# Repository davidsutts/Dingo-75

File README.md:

# Dingo-75

The Dingo 75 is intended to be a budget 75% keyboard PCB that anyone can print and assemble. The PCB runs on an Atmel AT90USB1286.

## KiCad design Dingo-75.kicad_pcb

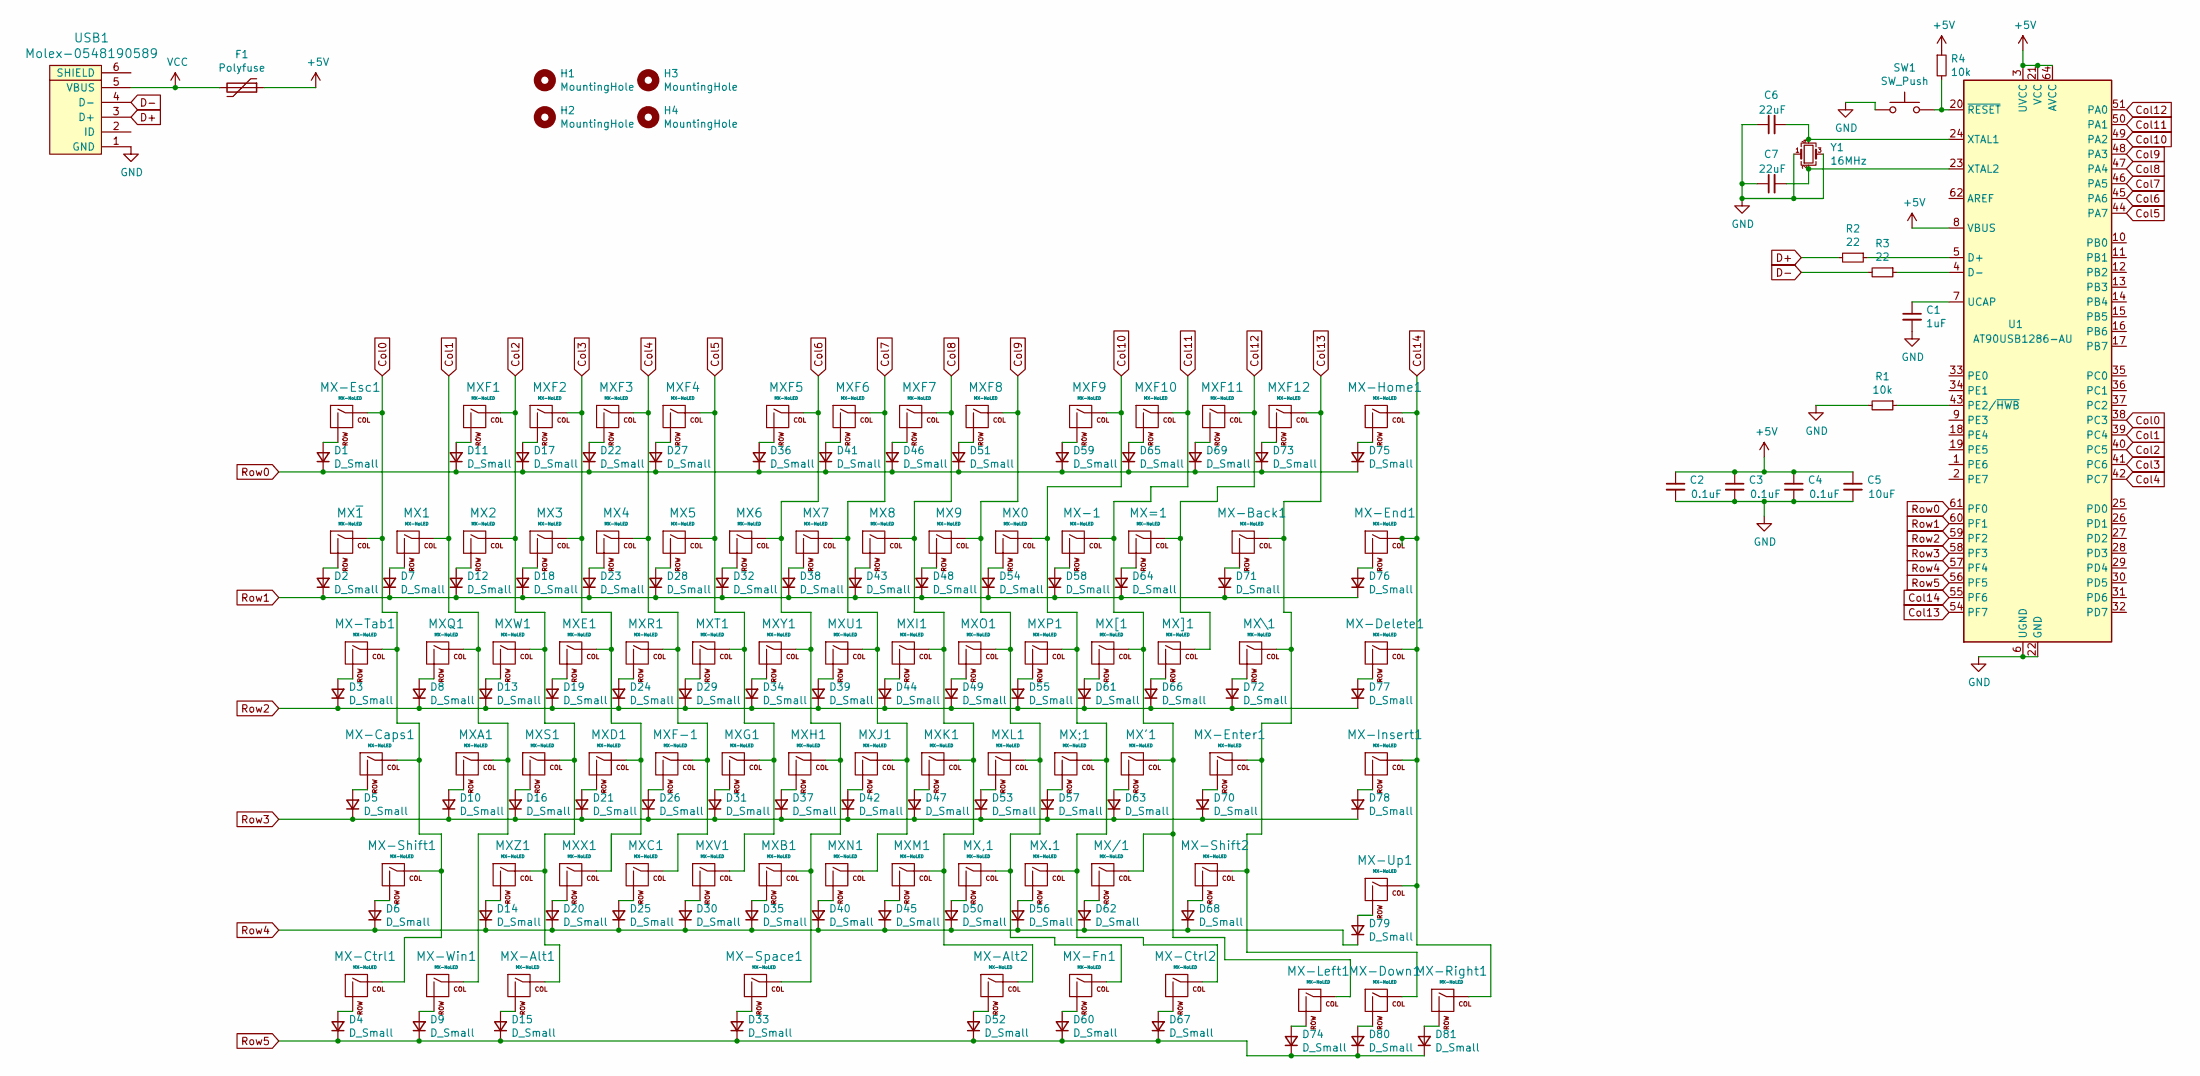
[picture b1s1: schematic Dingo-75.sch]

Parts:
C1: 1uF; C_0805_2012Metric
C2, C3, C4: 0.1uF; C_0805_2012Metric
C5: 10uF; C_0805_2012Metric
C6, C7: 22uF; C_0805_2012Metric
D1, D2, D3, D4, D5, D6, D7, D8, D9, D10, D11, D12, D13, D14, D15, D16, D17, D18, D19, D20, D21, D22, D23, D24, D25, D26, D27, D28, D29, D30, D31, D32, D33, D34, D35, D36, D37, D38, D39, D40, D41, D42, D43, D44, D45, D46, D47, D48, D49, D50, D51, D52, D53, D54, D55, D56, D57, D58, D59, D60, D61, D62, D63, D64, D65, D66, D67, D68, D69, D70, D71, D72, D73, D74, D75, D76, D77, D78, D79, D80, D81: D_Small; D_SOD-123
F1: Polyfuse; Fuse_1206_3216Metric
H1, H2, H3, H4: MountingHole; MountingHole_2mm
MX0, MX1, MX2, MX3, MX4, MX5, MX6, MX7, MX8, MX9, MX.1: MX-NoLED; MX-1U-NoLED
MX'1: MX-NoLED; MX-1U-NoLED
MX,1: MX-NoLED; MX-1U-NoLED
MX-1: MX-NoLED; MX-1U-NoLED
MX-Alt1, MX-Alt2: MX-NoLED; MX-1U-NoLED
MX-Back1: MX-NoLED; MX-1U-NoLED
MX-Caps1: MX-NoLED; MX-1U-NoLED
MX-Ctrl1, MX-Ctrl2: MX-NoLED; MX-1U-NoLED
MX-Delete1: MX-NoLED; MX-1U-NoLED
MX-Down1: MX-NoLED; MX-1U-NoLED
MX-End1: MX-NoLED; MX-1U-NoLED
MX-Enter1: MX-NoLED; MX-1U-NoLED
MX-Esc1: MX-NoLED; MX-1U-NoLED
MX-Fn1: MX-NoLED; MX-1U-NoLED
MX-Home1: MX-NoLED; MX-1U-NoLED
MX-Insert1: MX-NoLED; MX-1U-NoLED
MX-Left1: MX-NoLED; MX-1U-NoLED
MX-Right1: MX-NoLED; MX-1U-NoLED
MX-Shift1, MX-Shift2: MX-NoLED; MX-1U-NoLED
MX-Space1: MX-NoLED; MX-1U-NoLED
MX-Tab1: MX-NoLED; MX-1U-NoLED
MX-Up1: MX-NoLED; MX-1U-NoLED
MX-Win1: MX-NoLED; MX-1U-NoLED
MX/1: MX-NoLED; MX-1U-NoLED
MX;1: MX-NoLED; MX-1U-NoLED
MX=1: MX-NoLED; MX-1U-NoLED
MXA1: MX-NoLED; MX-1U-NoLED
MXB1: MX-NoLED; MX-1U-NoLED
MXC1: MX-NoLED; MX-1U-NoLED
MXD1: MX-NoLED; MX-1U-NoLED
MXE1: MX-NoLED; MX-1U-NoLED
MXF1, MXF2, MXF3, MXF4, MXF5, MXF6, MXF7, MXF8, MXF9, MXF10, MXF11, MXF12: MX-NoLED; MX-1U-NoLED
MXF-1: MX-NoLED; MX-1U-NoLED
MXG1: MX-NoLED; MX-1U-NoLED
MXH1: MX-NoLED; MX-1U-NoLED
MXI1: MX-NoLED; MX-1U-NoLED
MXJ1: MX-NoLED; MX-1U-NoLED
MXK1: MX-NoLED; MX-1U-NoLED
MXL1: MX-NoLED; MX-1U-NoLED
MXM1: MX-NoLED; MX-1U-NoLED
MXN1: MX-NoLED; MX-1U-NoLED
MXO1: MX-NoLED; MX-1U-NoLED
MXP1: MX-NoLED; MX-1U-NoLED
MXQ1: MX-NoLED; MX-1U-NoLED
MXR1: MX-NoLED; MX-1U-NoLED
MXS1: MX-NoLED; MX-1U-NoLED
MXT1: MX-NoLED; MX-1U-NoLED
MXU1: MX-NoLED; MX-1U-NoLED
MXV1: MX-NoLED; MX-1U-NoLED
MXW1: MX-NoLED; MX-1U-NoLED
MXX1: MX-NoLED; MX-1U-NoLED
MXY1: MX-NoLED; MX-1U-NoLED
MXZ1: MX-NoLED; MX-1U-NoLED
MX[1: MX-NoLED; MX-1U-NoLED
MX\1: MX-NoLED; MX-1U-NoLED
MX]1: MX-NoLED; MX-1U-NoLED
MX~1: MX-NoLED; MX-1U-NoLED
R1, R4: 10k; R_0805_2012Metric
R2, R3: 22; R_0805_2012Metric
SW1: SW_Push; SKQG-1155865
U1: AT90USB1286-AU; TQFP-64_14x14mm_P0.8mm
USB1: Molex-0548190589
Y1: 16MHz; Crystal_SMD_3225-4Pin_3.2x2.5mm

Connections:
+5V: C2.1, C3.1, C4.1, C5.1, F1.1, R4.1, U1.3 (UVCC), U1.8 (VBUS), U1.21 (VCC), U1.52 (VCC), U1.64 (AVCC)
Col0: MX-Caps1.1 (COL), MX-Ctrl1.1 (COL), MX-Esc1.1 (COL), MX-Shift1.1 (COL), MX-Tab1.1 (COL), MX~1.1 (COL), U1.38 (PC3)
Col1: MX1.1 (COL), MX-Win1.1 (COL), MXA1.1 (COL), MXQ1.1 (COL), U1.39 (PC4)
Col2: MX2.1 (COL), MX-Alt1.1 (COL), MXF1.1 (COL), MXS1.1 (COL), MXW1.1 (COL), MXZ1.1 (COL), U1.40 (PC5)
Col3: MX3.1 (COL), MXD1.1 (COL), MXE1.1 (COL), MXF2.1 (COL), MXX1.1 (COL), U1.41 (PC6)
Col4: MX4.1 (COL), MXC1.1 (COL), MXF3.1 (COL), MXF-1.1 (COL), MXR1.1 (COL), U1.42 (PC7)
Col5: MX5.1 (COL), MXF4.1 (COL), MXG1.1 (COL), MXT1.1 (COL), MXV1.1 (COL), U1.44 (PA7)
Col6: MX6.1 (COL), MX-Space1.1 (COL), MXB1.1 (COL), MXF5.1 (COL), MXH1.1 (COL), MXY1.1 (COL), U1.45 (PA6)
Col7: MX7.1 (COL), MXF6.1 (COL), MXJ1.1 (COL), MXN1.1 (COL), MXU1.1 (COL), U1.46 (PA5)
Col8: MX8.1 (COL), MX-Alt2.1 (COL), MXF7.1 (COL), MXI1.1 (COL), MXK1.1 (COL), MXM1.1 (COL), U1.47 (PA4)
Col9: MX9.1 (COL), MX,1.1 (COL), MX-Fn1.1 (COL), MXF8.1 (COL), MXL1.1 (COL), MXO1.1 (COL), U1.48 (PA3)
Col10: MX0.1 (COL), MX-Ctrl2.1 (COL), MX.1.1 (COL), MX;1.1 (COL), MXF9.1 (COL), MXP1.1 (COL), U1.49 (PA2)
Col11: MX'1.1 (COL), MX-1.1 (COL), MX-Left1.1 (COL), MX/1.1 (COL), MXF10.1 (COL), MX[1.1 (COL), U1.50 (PA1)
Col12: MX=1.1 (COL), MXF11.1 (COL), MX]1.1 (COL), U1.51 (PA0)
Col13: MX-Back1.1 (COL), MX-Down1.1 (COL), MX-Enter1.1 (COL), MX-Shift2.1 (COL), MXF12.1 (COL), MX\1.1 (COL), U1.54 (PF7)
Col14: MX-Delete1.1 (COL), MX-End1.1 (COL), MX-Home1.1 (COL), MX-Insert1.1 (COL), MX-Right1.1 (COL), MX-Up1.1 (COL), U1.55 (PF6)
D+: R2.2, USB1.3 (D+)
D-: R3.2, USB1.4 (D-)
GND: C1.2, C2.2, C3.2, C4.2, C5.2, C6.1, C7.1, R1.2, SW1.1, U1.6 (UGND), U1.22 (GND), U1.53 (GND), U1.63 (GND), USB1.1 (GND), Y1.1, Y1.3
unnamed: C1.1, U1.7 (UCAP)
unnamed: C6.2, U1.24 (XTAL1), Y1.4
unnamed: C7.2, U1.23 (XTAL2), Y1.2
unnamed: D1.2 (A), MX-Esc1.2 (ROW)
unnamed: D2.2 (A), MX~1.2 (ROW)
unnamed: D3.2 (A), MX-Tab1.2 (ROW)
unnamed: D4.2 (A), MX-Ctrl1.2 (ROW)
unnamed: D5.2 (A), MX-Caps1.2 (ROW)
unnamed: D6.2 (A), MX-Shift1.2 (ROW)
unnamed: D7.2 (A), MX1.2 (ROW)
unnamed: D8.2 (A), MXQ1.2 (ROW)
unnamed: D9.2 (A), MX-Win1.2 (ROW)
unnamed: D10.2 (A), MXA1.2 (ROW)
unnamed: D11.2 (A), MXF1.2 (ROW)
unnamed: D12.2 (A), MX2.2 (ROW)
unnamed: D13.2 (A), MXW1.2 (ROW)
unnamed: D14.2 (A), MXZ1.2 (ROW)
unnamed: D15.2 (A), MX-Alt1.2 (ROW)
unnamed: D16.2 (A), MXS1.2 (ROW)
unnamed: D17.2 (A), MXF2.2 (ROW)
unnamed: D18.2 (A), MX3.2 (ROW)
unnamed: D19.2 (A), MXE1.2 (ROW)
unnamed: D20.2 (A), MXX1.2 (ROW)
unnamed: D21.2 (A), MXD1.2 (ROW)
unnamed: D22.2 (A), MXF3.2 (ROW)
unnamed: D23.2 (A), MX4.2 (ROW)
unnamed: D24.2 (A), MXR1.2 (ROW)
unnamed: D25.2 (A), MXC1.2 (ROW)
unnamed: D26.2 (A), MXF-1.2 (ROW)
unnamed: D27.2 (A), MXF4.2 (ROW)
unnamed: D28.2 (A), MX5.2 (ROW)
unnamed: D29.2 (A), MXT1.2 (ROW)
unnamed: D30.2 (A), MXV1.2 (ROW)
unnamed: D31.2 (A), MXG1.2 (ROW)
unnamed: D32.2 (A), MX6.2 (ROW)
unnamed: D33.2 (A), MX-Space1.2 (ROW)
unnamed: D34.2 (A), MXY1.2 (ROW)
unnamed: D35.2 (A), MXB1.2 (ROW)
unnamed: D36.2 (A), MXF5.2 (ROW)
unnamed: D37.2 (A), MXH1.2 (ROW)
unnamed: D38.2 (A), MX7.2 (ROW)
unnamed: D39.2 (A), MXU1.2 (ROW)
unnamed: D40.2 (A), MXN1.2 (ROW)
unnamed: D41.2 (A), MXF6.2 (ROW)
unnamed: D42.2 (A), MXJ1.2 (ROW)
unnamed: D43.2 (A), MX8.2 (ROW)
unnamed: D44.2 (A), MXI1.2 (ROW)
unnamed: D45.2 (A), MXM1.2 (ROW)
unnamed: D46.2 (A), MXF7.2 (ROW)
unnamed: D47.2 (A), MXK1.2 (ROW)
unnamed: D48.2 (A), MX9.2 (ROW)
unnamed: D49.2 (A), MXO1.2 (ROW)
unnamed: D50.2 (A), MX,1.2 (ROW)
unnamed: D51.2 (A), MXF8.2 (ROW)
unnamed: D52.2 (A), MX-Alt2.2 (ROW)
unnamed: D53.2 (A), MXL1.2 (ROW)
unnamed: D54.2 (A), MX0.2 (ROW)
unnamed: D55.2 (A), MXP1.2 (ROW)
unnamed: D56.2 (A), MX.1.2 (ROW)
unnamed: D57.2 (A), MX;1.2 (ROW)
unnamed: D58.2 (A), MX-1.2 (ROW)
unnamed: D59.2 (A), MXF9.2 (ROW)
unnamed: D60.2 (A), MX-Fn1.2 (ROW)
unnamed: D61.2 (A), MX[1.2 (ROW)
unnamed: D62.2 (A), MX/1.2 (ROW)
unnamed: D63.2 (A), MX'1.2 (ROW)
unnamed: D64.2 (A), MX=1.2 (ROW)
unnamed: D65.2 (A), MXF10.2 (ROW)
unnamed: D66.2 (A), MX]1.2 (ROW)
unnamed: D67.2 (A), MX-Ctrl2.2 (ROW)
unnamed: D68.2 (A), MX-Shift2.2 (ROW)
unnamed: D69.2 (A), MXF11.2 (ROW)
unnamed: D70.2 (A), MX-Enter1.2 (ROW)
unnamed: D71.2 (A), MX-Back1.2 (ROW)
unnamed: D72.2 (A), MX\1.2 (ROW)
unnamed: D73.2 (A), MXF12.2 (ROW)
unnamed: D74.2 (A), MX-Left1.2 (ROW)
unnamed: D75.2 (A), MX-Home1.2 (ROW)
unnamed: D76.2 (A), MX-End1.2 (ROW)
unnamed: D77.2 (A), MX-Delete1.2 (ROW)
unnamed: D78.2 (A), MX-Insert1.2 (ROW)
unnamed: D79.2 (A), MX-Up1.2 (ROW)
unnamed: D80.2 (A), MX-Down1.2 (ROW)
unnamed: D81.2 (A), MX-Right1.2 (ROW)
unnamed: R1.1, U1.43 (PE2/~HWB)
unnamed: R2.1, U1.5 (D+)
unnamed: R3.1, U1.4 (D-)
unnamed: R4.2, SW1.2, U1.20 (~RESET)
Row0: D1.1 (K), D11.1 (K), D17.1 (K), D22.1 (K), D27.1 (K), D36.1 (K), D41.1 (K), D46.1 (K), D51.1 (K), D59.1 (K), D65.1 (K), D69.1 (K), D73.1 (K), D75.1 (K), U1.61 (PF0)
Row1: D2.1 (K), D7.1 (K), D12.1 (K), D18.1 (K), D23.1 (K), D28.1 (K), D32.1 (K), D38.1 (K), D43.1 (K), D48.1 (K), D54.1 (K), D58.1 (K), D64.1 (K), D71.1 (K), D76.1 (K), U1.60 (PF1)
Row2: D3.1 (K), D8.1 (K), D13.1 (K), D19.1 (K), D24.1 (K), D29.1 (K), D34.1 (K), D39.1 (K), D44.1 (K), D49.1 (K), D55.1 (K), D61.1 (K), D66.1 (K), D72.1 (K), D77.1 (K), U1.59 (PF2)
Row3: D5.1 (K), D10.1 (K), D16.1 (K), D21.1 (K), D26.1 (K), D31.1 (K), D37.1 (K), D42.1 (K), D47.1 (K), D53.1 (K), D57.1 (K), D63.1 (K), D70.1 (K), D78.1 (K), U1.58 (PF3)
Row4: D6.1 (K), D14.1 (K), D20.1 (K), D25.1 (K), D30.1 (K), D35.1 (K), D40.1 (K), D45.1 (K), D50.1 (K), D56.1 (K), D62.1 (K), D68.1 (K), D79.1 (K), U1.57 (PF4)
Row5: D4.1 (K), D9.1 (K), D15.1 (K), D33.1 (K), D52.1 (K), D60.1 (K), D67.1 (K), D74.1 (K), D80.1 (K), D81.1 (K), U1.56 (PF5)
VCC: F1.2, USB1.5 (VBUS)

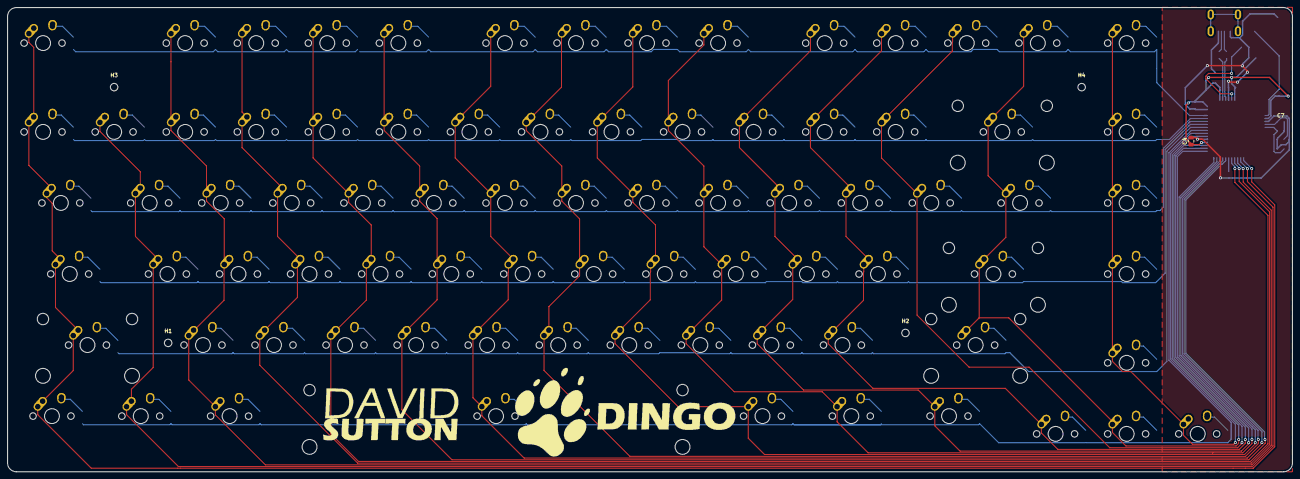
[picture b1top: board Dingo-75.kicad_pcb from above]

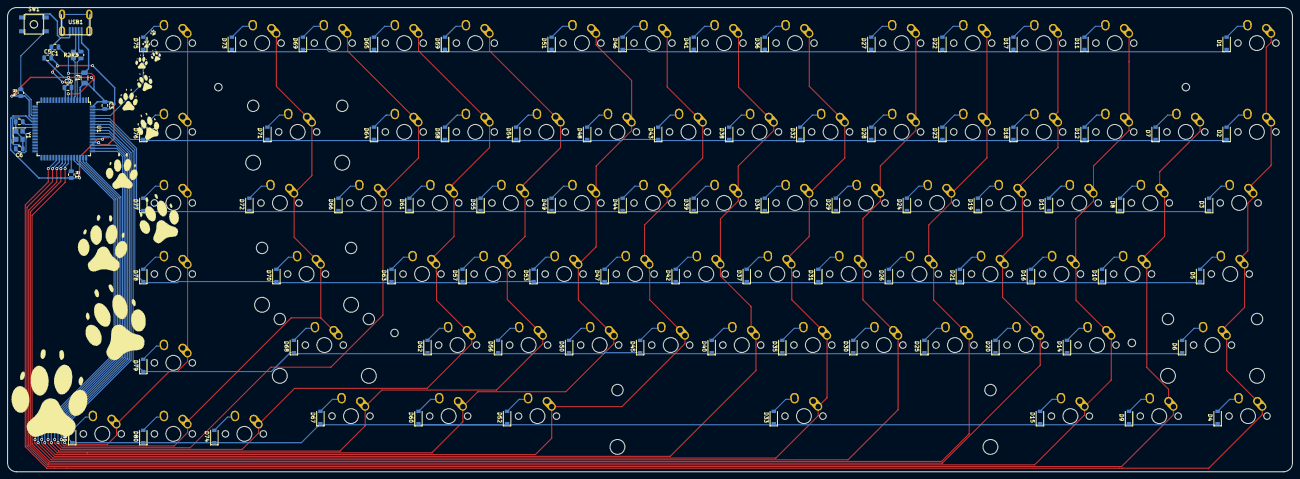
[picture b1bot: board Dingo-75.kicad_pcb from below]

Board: 2 copper layers, 344.5 x 124.5 mm, 182 parts (96 on the bottom side), 114 nets.

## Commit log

2022-01-26 Created initial project files
2022-01-26 Added submodules for footprints
2022-01-26 Setup project
2022-02-06 Finished MCU setup, and started switch matrix
2022-02-07 Completed switch matrix, started footprint assignment
2022-02-10 Completed Footprint Assignment, Completed Board Layout, Started trace routing
2022-02-11 Completed routing
2022-02-11 FINISHED V1
2022-02-12 Added finishing touches, including Silkscreening using Images
